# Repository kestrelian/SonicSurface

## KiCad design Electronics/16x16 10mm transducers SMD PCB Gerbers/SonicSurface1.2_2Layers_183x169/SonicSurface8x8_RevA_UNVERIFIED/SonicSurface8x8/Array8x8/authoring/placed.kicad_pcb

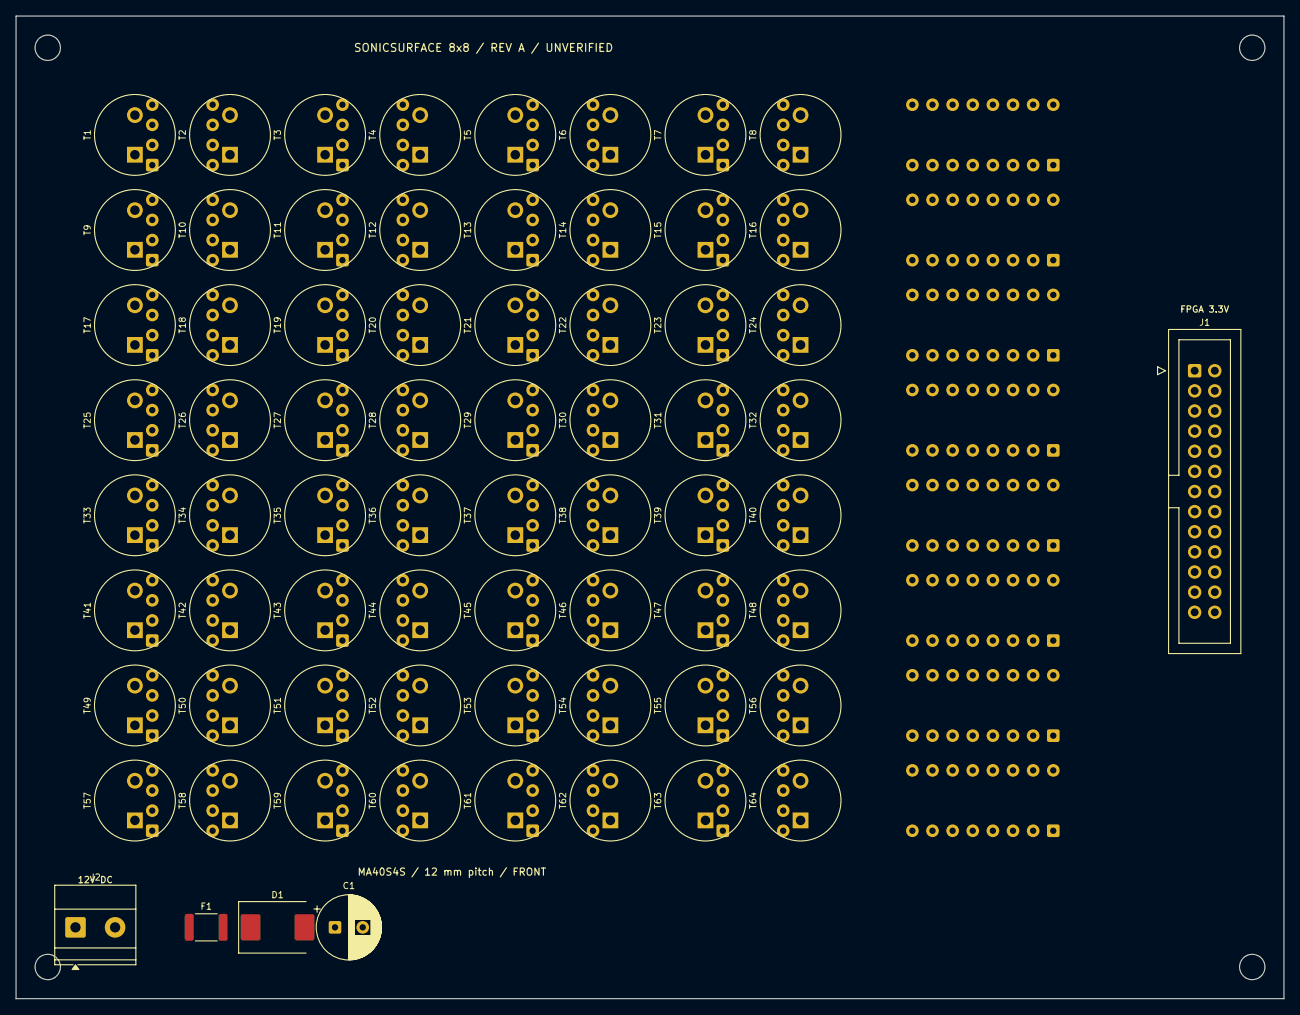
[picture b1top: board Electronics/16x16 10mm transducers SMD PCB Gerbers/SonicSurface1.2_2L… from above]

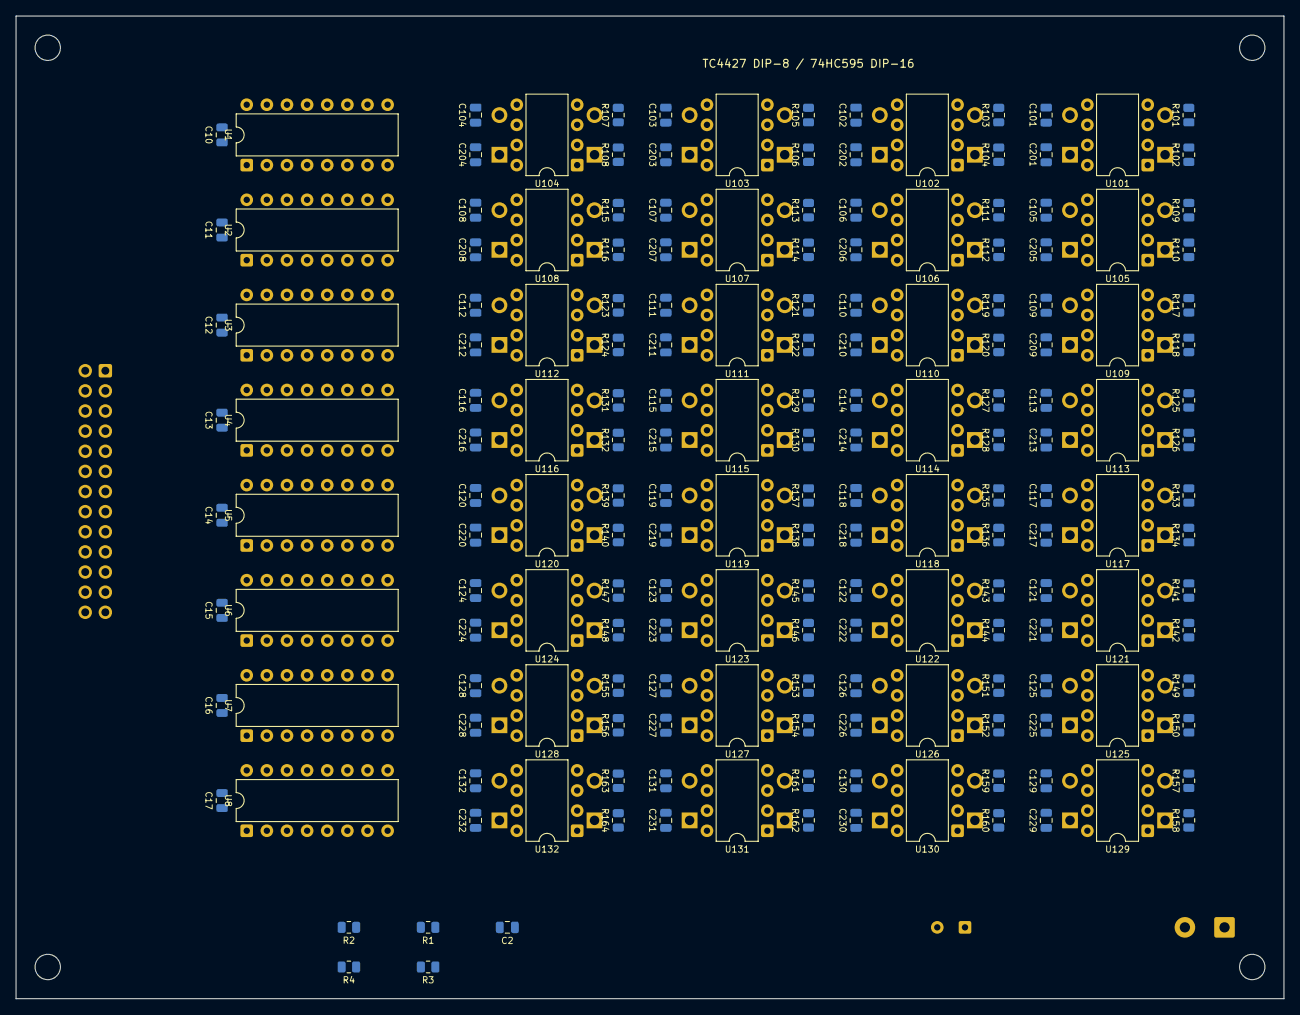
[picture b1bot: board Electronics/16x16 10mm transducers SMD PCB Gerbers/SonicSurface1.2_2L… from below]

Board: 2 copper layers, 160.0 x 124.0 mm, 254 parts (181 on the bottom side), 145 nets, no tracks yet.

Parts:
C1: 220uF 35V low ESR; CP_Radial_D8.0mm_P3.50mm
C2: 10uF 10V X7R; C_0805_2012Metric
C10, C11, C12, C13, C14, C15, C16, C17, C101, C102, C103, C104, C105, C106, C107, C108, C109, C110, C111, C112, C113, C114, C115, C116, C117, C118, C119, C120, C121, C122, C123, C124, C125, C126, C127, C128, C129, C130, C131, C132: 100nF 50V X7R; C_0805_2012Metric
C201, C202, C203, C204, C205, C206, C207, C208, C209, C210, C211, C212, C213, C214, C215, C216, C217, C218, C219, C220, C221, C222, C223, C224, C225, C226, C227, C228, C229, C230, C231, C232: 1uF 50V X7R; C_0805_2012Metric
D1: SS34 / SMC; D_SMC
F1: 1A fast / 1812; Fuse_1812_4532Metric
H1, H2, H3, H4: MountingHole_3.2mm_M3
J1: IDC26 / FPGA CABLE; IDC-Header_2x13_P2.54mm_Vertical
J2: 12V DC INPUT; TerminalBlock_Phoenix_MKDS-1,5-2_1x02_P5.00mm_Horizontal
R1, R2, R3, R4, R101, R102, R103, R104, R105, R106, R107, R108, R109, R110, R111, R112, R113, R114, R115, R116, R117, R118, R119, R120, R121, R122, R123, R124, R125, R126, R127, R128, R129, R130, R131, R132, R133, R134, R135, R136, R137, R138, R139, R140, R141, R142, R143, R144, R145, R146, R147, R148, R149, R150, R151, R152, R153, R154, R155, R156, R157, R158, R159, R160, R161, R162, R163, R164: 10k; R_0805_2012Metric
T1, T2, T3, T4, T5, T6, T7, T8, T9, T10, T11, T12, T13, T14, T15, T16, T17, T18, T19, T20, T21, T22, T23, T24, T25, T26, T27, T28, T29, T30, T31, T32, T33, T34, T35, T36, T37, T38, T39, T40, T41, T42, T43, T44, T45, T46, T47, T48, T49, T50, T51, T52, T53, T54, T55, T56, T57, T58, T59, T60, T61, T62, T63, T64: MA40S4S; MA40S4S_P5mm
U1, U2, U3, U4, U5, U6, U7, U8: 74HC595N / DIP-16; DIP-16_W7.62mm
U101, U102, U103, U104, U105, U106, U107, U108, U109, U110, U111, U112, U113, U114, U115, U116, U117, U118, U119, U120, U121, U122, U123, U124, U125, U126, U127, U128, U129, U130, U131, U132: TC4427EPA / DIP-8; DIP-8_W7.62mm

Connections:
+3V3: C2.1, C10.1, C11.1, C12.1, C13.1, C14.1, C15.1, C16.1, C17.1, J1.1, R1.1, U1.16, U2.16, U3.16, U4.16, U5.16, U6.16, U7.16, U8.16
+12V: C1.1, C101.1, C102.1, C103.1, C104.1, C105.1, C106.1, C107.1, C108.1, C109.1, C110.1, C111.1, C112.1, C113.1, C114.1, C115.1, C116.1, C117.1, C118.1, C119.1, C120.1, C121.1, C122.1, C123.1, C124.1, C125.1, C126.1, C127.1, C128.1, C129.1, C130.1, C131.1, C132.1, C201.1, C202.1, C203.1, C204.1, C205.1, C206.1, C207.1, C208.1, C209.1, C210.1, C211.1, C212.1, C213.1, C214.1, C215.1, C216.1, C217.1, C218.1, C219.1, C220.1, C221.1, C222.1, C223.1, C224.1, C225.1, C226.1, C227.1, C228.1, C229.1, C230.1, C231.1, C232.1, D1.1, U101.6, U102.6, U103.6, U104.6, U105.6, U106.6, U107.6, U108.6, U109.6, U110.6, U111.6, U112.6, U113.6, U114.6, U115.6, U116.6, U117.6, U118.6, U119.6, U120.6, U121.6, U122.6, U123.6, U124.6, U125.6, U126.6, U127.6, U128.6, U129.6, U130.6, U131.6, U132.6
CLR_N: J1.25, R2.1, U1.10, U2.10, U3.10, U4.10, U5.10, U6.10, U7.10, U8.10
DATA0: J1.3, U1.14
DATA1: J1.5, U2.14
DATA2: J1.7, U3.14
DATA3: J1.9, U4.14
DATA4: J1.11, U5.14
DATA5: J1.13, U6.14
DATA6: J1.15, U7.14
DATA7: J1.17, U8.14
DRV00: T1.1, U101.7
DRV01: T2.1, U101.5
DRV02: T3.1, U102.7
DRV03: T4.1, U102.5
DRV04: T5.1, U103.7
DRV05: T6.1, U103.5
DRV06: T7.1, U104.7
DRV07: T8.1, U104.5
DRV08: T9.1, U105.7
DRV09: T10.1, U105.5
DRV10: T11.1, U106.7
DRV11: T12.1, U106.5
DRV12: T13.1, U107.7
DRV13: T14.1, U107.5
DRV14: T15.1, U108.7
DRV15: T16.1, U108.5
DRV16: T17.1, U109.7
DRV17: T18.1, U109.5
DRV18: T19.1, U110.7
DRV19: T20.1, U110.5
DRV20: T21.1, U111.7
DRV21: T22.1, U111.5
DRV22: T23.1, U112.7
DRV23: T24.1, U112.5
DRV24: T25.1, U113.7
DRV25: T26.1, U113.5
DRV26: T27.1, U114.7
DRV27: T28.1, U114.5
DRV28: T29.1, U115.7
DRV29: T30.1, U115.5
DRV30: T31.1, U116.7
DRV31: T32.1, U116.5
DRV32: T33.1, U117.7
DRV33: T34.1, U117.5
DRV34: T35.1, U118.7
DRV35: T36.1, U118.5
DRV36: T37.1, U119.7
DRV37: T38.1, U119.5
DRV38: T39.1, U120.7
DRV39: T40.1, U120.5
DRV40: T41.1, U121.7
DRV41: T42.1, U121.5
DRV42: T43.1, U122.7
DRV43: T44.1, U122.5
DRV44: T45.1, U123.7
DRV45: T46.1, U123.5
DRV46: T47.1, U124.7
DRV47: T48.1, U124.5
DRV48: T49.1, U125.7
DRV49: T50.1, U125.5
DRV50: T51.1, U126.7
DRV51: T52.1, U126.5
DRV52: T53.1, U127.7
DRV53: T54.1, U127.5
DRV54: T55.1, U128.7
DRV55: T56.1, U128.5
DRV56: T57.1, U129.7
DRV57: T58.1, U129.5
DRV58: T59.1, U130.7
DRV59: T60.1, U130.5
DRV60: T61.1, U131.7
DRV61: T62.1, U131.5
DRV62: T63.1, U132.7
DRV63: T64.1, U132.5
GND: C1.2, C2.2, C10.2, C11.2, C12.2, C13.2, C14.2, C15.2, C16.2, C17.2, C101.2, C102.2, C103.2, C104.2, C105.2, C106.2, C107.2, C108.2, C109.2, C110.2, C111.2, C112.2, C113.2, C114.2, C115.2, C116.2, C117.2, C118.2, C119.2, C120.2, C121.2, C122.2, C123.2, C124.2, C125.2, C126.2, C127.2, C128.2, C129.2, C130.2, C131.2, C132.2, C201.2, C202.2, C203.2, C204.2, C205.2, C206.2, C207.2, C208.2, C209.2, C210.2, C211.2, C212.2, C213.2, C214.2, C215.2, C216.2, C217.2, C218.2, C219.2, C220.2, C221.2, C222.2, C223.2, C224.2, C225.2, C226.2, C227.2, C228.2, C229.2, C230.2, C231.2, C232.2, J1.2, J1.4, J1.6, J1.8, J1.10, J1.12, J1.14, J1.16, J1.18, J1.20, J1.22, J1.24, J1.26, J2.2, R2.2, R3.2, R4.2, R101.2, R102.2, R103.2, R104.2, R105.2, R106.2, R107.2, R108.2, R109.2, R110.2, R111.2, R112.2, R113.2, R114.2, R115.2, R116.2, R117.2, R118.2, R119.2, R120.2, R121.2, R122.2, R123.2, R124.2, R125.2, R126.2, R127.2, R128.2, R129.2, R130.2, R131.2, R132.2, R133.2, R134.2, R135.2, R136.2, R137.2, R138.2, R139.2, R140.2, R141.2, R142.2, R143.2, R144.2, R145.2, R146.2, R147.2, R148.2, R149.2, R150.2, R151.2, R152.2, R153.2, R154.2, R155.2, R156.2, R157.2, R158.2, R159.2, R160.2, R161.2, R162.2, R163.2, R164.2, T1.2, T2.2, T3.2, T4.2, T5.2, T6.2, T7.2, T8.2, T9.2, T10.2, T11.2, T12.2, T13.2, T14.2, T15.2, T16.2, T17.2, T18.2, T19.2, T20.2, T21.2, T22.2, T23.2, T24.2, T25.2, T26.2, T27.2, T28.2, T29.2, T30.2, T31.2, T32.2, T33.2, T34.2, T35.2, T36.2, T37.2, T38.2, T39.2, T40.2, T41.2, T42.2, T43.2, T44.2, T45.2, T46.2, T47.2, T48.2, T49.2, T50.2, T51.2, T52.2, T53.2, T54.2, T55.2, T56.2, T57.2, T58.2, T59.2, T60.2, T61.2, T62.2, T63.2, T64.2, U1.8, U2.8, U3.8, U4.8, U5.8, U6.8, U7.8, U8.8, U101.3, U102.3, U103.3, U104.3, U105.3, U106.3, U107.3, U108.3, U109.3, U110.3, U111.3, U112.3, U113.3, U114.3, U115.3, U116.3, U117.3, U118.3, U119.3, U120.3, U121.3, U122.3, U123.3, U124.3, U125.3, U126.3, U127.3, U128.3, U129.3, U130.3, U131.3, U132.3
LATCH: J1.21, R4.1, U1.12, U2.12, U3.12, U4.12, U5.12, U6.12, U7.12, U8.12
OE_N: J1.23, R1.2, U1.13, U2.13, U3.13, U4.13, U5.13, U6.13, U7.13, U8.13
Q00: R101.1, U1.15, U101.2
Q01: R102.1, U1.1, U101.4
Q02: R103.1, U1.2, U102.2
Q03: R104.1, U1.3, U102.4
Q04: R105.1, U1.4, U103.2
Q05: R106.1, U1.5, U103.4
Q06: R107.1, U1.6, U104.2
Q07: R108.1, U1.7, U104.4
Q08: R109.1, U2.15, U105.2
Q09: R110.1, U2.1, U105.4
Q10: R111.1, U2.2, U106.2
Q11: R112.1, U2.3, U106.4
Q12: R113.1, U2.4, U107.2
Q13: R114.1, U2.5, U107.4
Q14: R115.1, U2.6, U108.2
Q15: R116.1, U2.7, U108.4
Q16: R117.1, U3.15, U109.2
Q17: R118.1, U3.1, U109.4
Q18: R119.1, U3.2, U110.2
Q19: R120.1, U3.3, U110.4
Q20: R121.1, U3.4, U111.2
Q21: R122.1, U3.5, U111.4
Q22: R123.1, U3.6, U112.2
Q23: R124.1, U3.7, U112.4
Q24: R125.1, U4.15, U113.2
Q25: R126.1, U4.1, U113.4
Q26: R127.1, U4.2, U114.2
Q27: R128.1, U4.3, U114.4
Q28: R129.1, U4.4, U115.2
Q29: R130.1, U4.5, U115.4
Q30: R131.1, U4.6, U116.2
Q31: R132.1, U4.7, U116.4
Q32: R133.1, U5.15, U117.2
Q33: R134.1, U5.1, U117.4
Q34: R135.1, U5.2, U118.2
Q35: R136.1, U5.3, U118.4
Q36: R137.1, U5.4, U119.2
Q37: R138.1, U5.5, U119.4
Q38: R139.1, U5.6, U120.2
Q39: R140.1, U5.7, U120.4
Q40: R141.1, U6.15, U121.2
Q41: R142.1, U6.1, U121.4
Q42: R143.1, U6.2, U122.2
Q43: R144.1, U6.3, U122.4
Q44: R145.1, U6.4, U123.2
Q45: R146.1, U6.5, U123.4
Q46: R147.1, U6.6, U124.2
Q47: R148.1, U6.7, U124.4
Q48: R149.1, U7.15, U125.2
Q49: R150.1, U7.1, U125.4
Q50: R151.1, U7.2, U126.2
Q51: R152.1, U7.3, U126.4
Q52: R153.1, U7.4, U127.2
Q53: R154.1, U7.5, U127.4
Q54: R155.1, U7.6, U128.2
Q55: R156.1, U7.7, U128.4
Q56: R157.1, U8.15, U129.2
Q57: R158.1, U8.1, U129.4
Q58: R159.1, U8.2, U130.2
Q59: R160.1, U8.3, U130.4
Q60: R161.1, U8.4, U131.2
Q61: R162.1, U8.5, U131.4
Q62: R163.1, U8.6, U132.2
Q63: R164.1, U8.7, U132.4
SCLK: J1.19, R3.1, U1.11, U2.11, U3.11, U4.11, U5.11, U6.11, U7.11, U8.11
VFUSED: D1.2, F1.2
VIN: F1.1, J2.1

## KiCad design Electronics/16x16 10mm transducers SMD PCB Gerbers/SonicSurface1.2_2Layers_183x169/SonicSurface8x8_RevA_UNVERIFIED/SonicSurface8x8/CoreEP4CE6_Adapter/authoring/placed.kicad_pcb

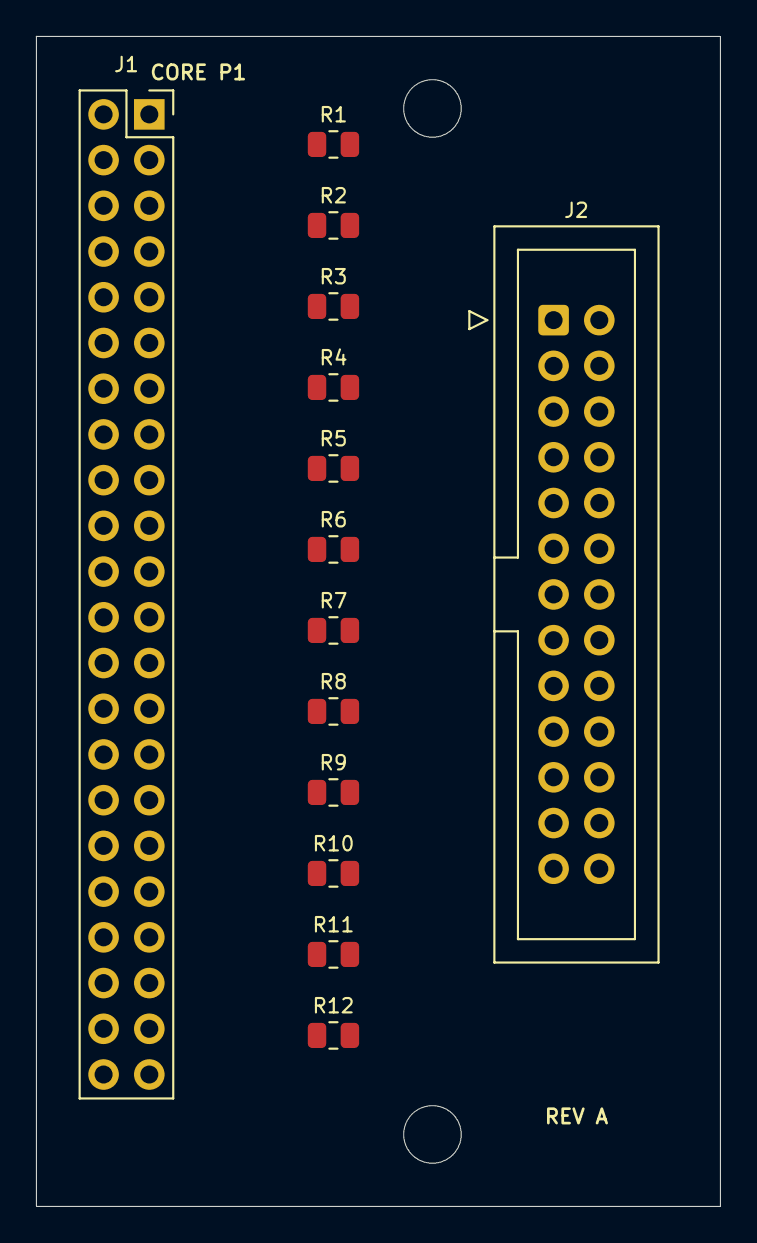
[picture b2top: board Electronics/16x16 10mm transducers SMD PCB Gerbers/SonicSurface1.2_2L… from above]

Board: 2 copper layers, 38.0 x 65.0 mm, 16 parts (0 on the bottom side), 26 nets, no tracks yet.

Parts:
H1, H2: MountingHole_3.2mm_M3
J1: CoreEP4CE6 P1 ONLY; PinSocket_2x22_P2.54mm_Vertical
J2: IDC26 to ARRAY J1; IDC-Header_2x13_P2.54mm_Vertical
R1, R2, R3, R4, R5, R6, R7, R8, R9, R10, R11, R12: 33R source termination; R_0805_2012Metric

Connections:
+3V3: J1.2, J2.1
CLR_N: J2.25, R12.2
CLR_N_SRC: J1.20, R12.1
DATA0: J2.3, R1.2
DATA0_SRC: J1.3, R1.1
DATA1: J2.5, R2.2
DATA1_SRC: J1.5, R2.1
DATA2: J2.7, R3.2
DATA2_SRC: J1.7, R3.1
DATA3: J2.9, R4.2
DATA3_SRC: J1.9, R4.1
DATA4: J2.11, R5.2
DATA4_SRC: J1.11, R5.1
DATA5: J2.13, R6.2
DATA5_SRC: J1.13, R6.1
DATA6: J2.15, R7.2
DATA6_SRC: J1.15, R7.1
DATA7: J2.17, R8.2
DATA7_SRC: J1.17, R8.1
GND: J1.1, J1.23, J2.2, J2.4, J2.6, J2.8, J2.10, J2.12, J2.14, J2.16, J2.18, J2.20, J2.22, J2.24, J2.26
LATCH: J2.21, R10.2
LATCH_SRC: J1.22, R10.1
OE_N: J2.23, R11.2
OE_N_SRC: J1.19, R11.1
SCLK: J2.19, R9.2
SCLK_SRC: J1.21, R9.1

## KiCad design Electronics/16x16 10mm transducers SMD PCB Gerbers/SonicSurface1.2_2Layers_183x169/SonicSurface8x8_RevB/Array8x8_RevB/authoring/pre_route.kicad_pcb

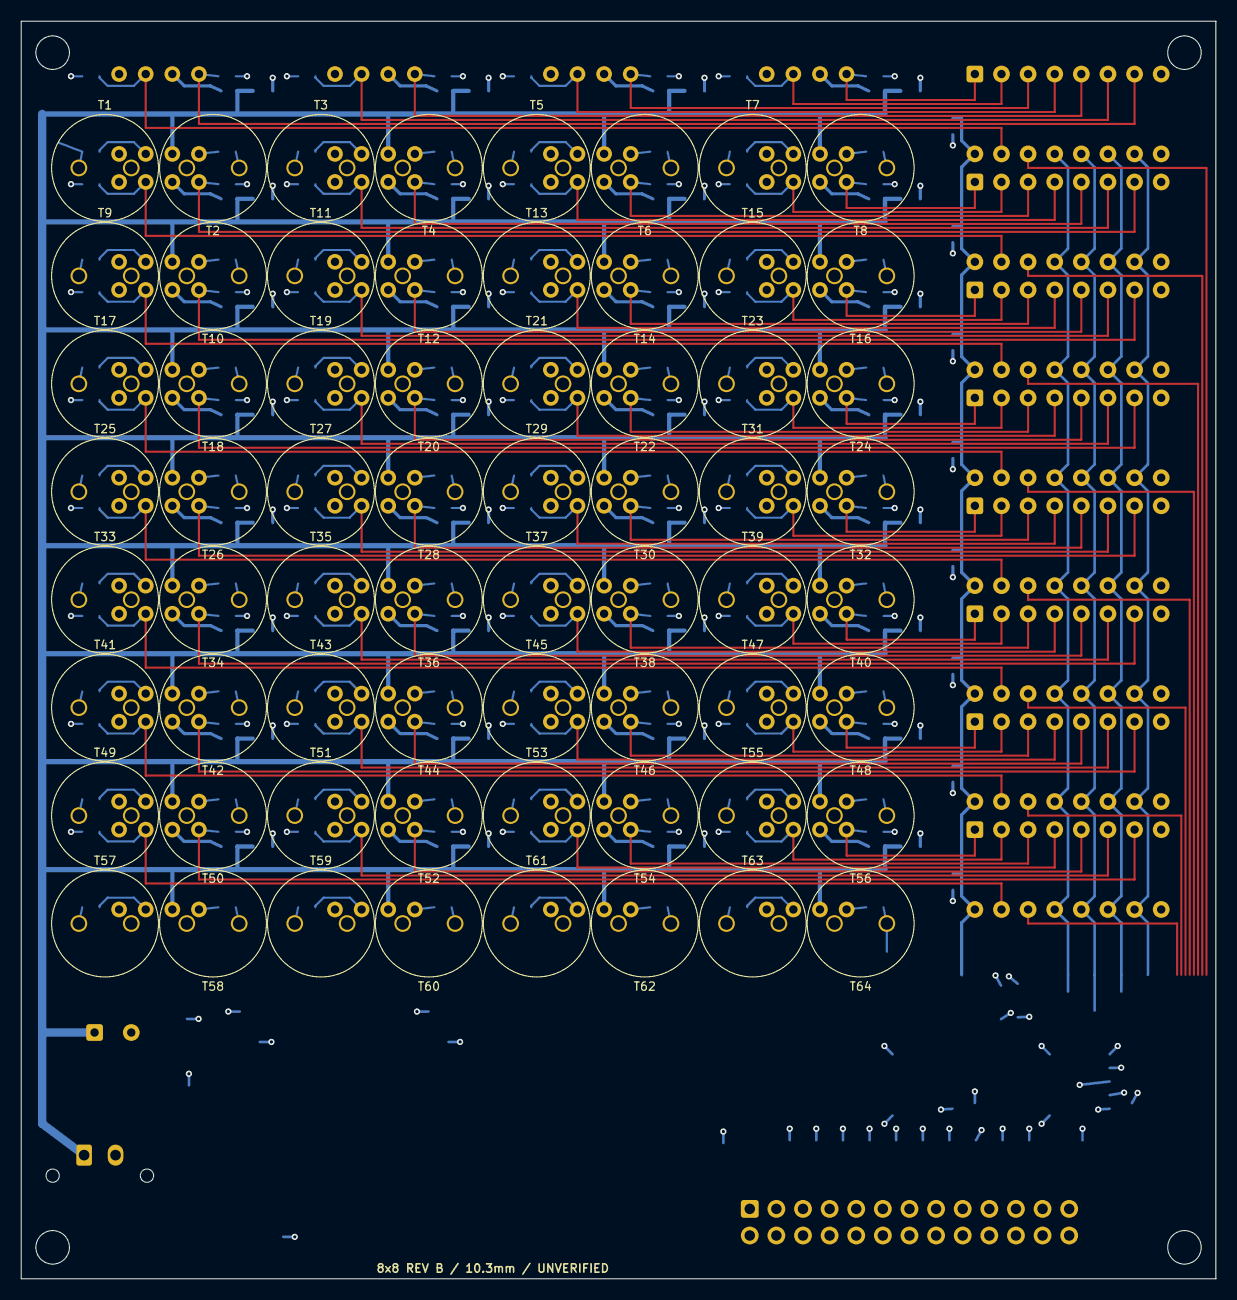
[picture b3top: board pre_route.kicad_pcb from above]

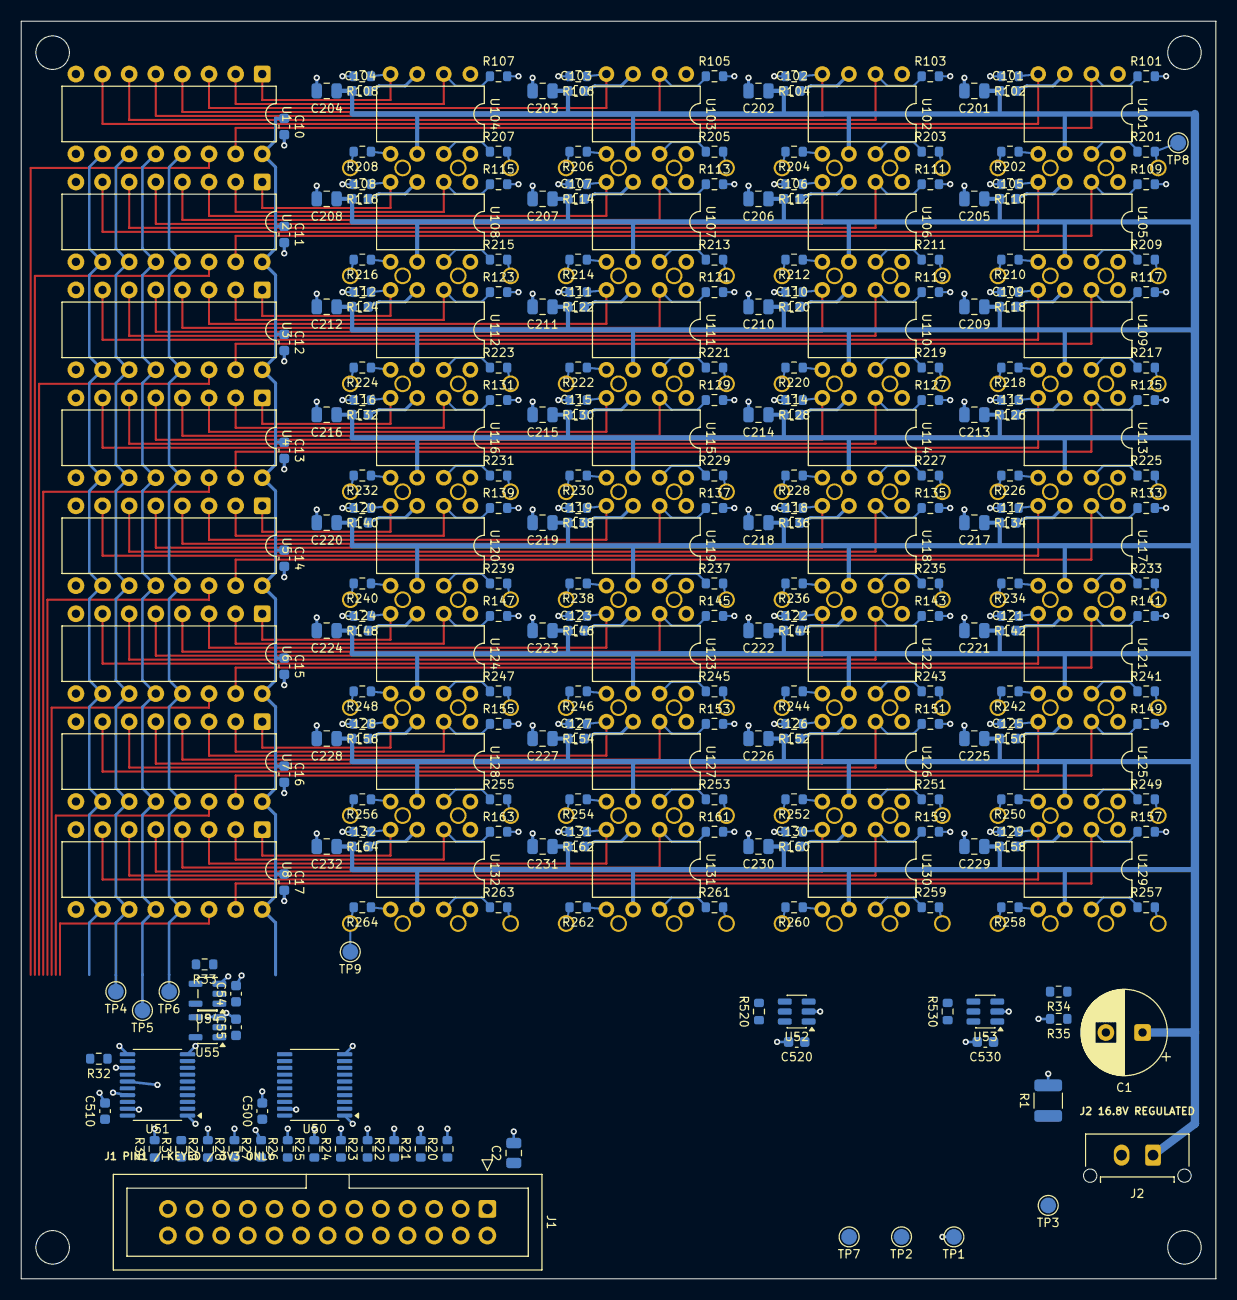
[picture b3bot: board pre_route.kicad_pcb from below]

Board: 2 copper layers, 114.0 x 120.0 mm, 352 parts (284 on the bottom side), 224 nets.

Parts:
C1: 220uF 35V low ESR; CP_Radial_D8.0mm_P3.50mm
C2: 10uF 10V X7R; C_0805_2012Metric
C10, C11, C12, C13, C14, C15, C16, C17, C54, C55, C101, C102, C103, C104, C105, C106, C107, C108, C109, C110, C111, C112, C113, C114, C115, C116, C117, C118, C119, C120, C121, C122, C123, C124, C125, C126, C127, C128, C129, C130, C131, C132, C500, C510, C520, C530: 100nF 50V X7R; C_0603_1608Metric
C201, C202, C203, C204, C205, C206, C207, C208, C209, C210, C211, C212, C213, C214, C215, C216, C217, C218, C219, C220, C221, C222, C223, C224, C225, C226, C227, C228, C229, C230, C231, C232: 1uF 50V X7R; C_0805_2012Metric
H1, H2, H3, H4: MountingHole_3.2mm_M3
J1: KEYED IDC26 / 100mm MAX; IDC-Header_2x13_P2.54mm_Vertical
J2: REGULATED DRIVER POWER ONLY; FP_910b6471cdf1
R1: 2.2k 0.5W discharge; R_1210_3225Metric
R20, R21, R22, R23, R24, R25, R26, R27, R28, R29, R30: 100k; R_0603_1608Metric
R31, R32, R33, R101, R102, R103, R104, R105, R106, R107, R108, R109, R110, R111, R112, R113, R114, R115, R116, R117, R118, R119, R120, R121, R122, R123, R124, R125, R126, R127, R128, R129, R130, R131, R132, R133, R134, R135, R136, R137, R138, R139, R140, R141, R142, R143, R144, R145, R146, R147, R148, R149, R150, R151, R152, R153, R154, R155, R156, R157, R158, R159, R160, R161, R162, R163, R164, R520, R530: 10k; R_0603_1608Metric
R34: 374k 0.1%; R_0603_1608Metric
R35: 10k 0.1%; R_0603_1608Metric
R201, R202, R203, R204, R205, R206, R207, R208, R209, R210, R211, R212, R213, R214, R215, R216, R217, R218, R219, R220, R221, R222, R223, R224, R225, R226, R227, R228, R229, R230, R231, R232, R233, R234, R235, R236, R237, R238, R239, R240, R241, R242, R243, R244, R245, R246, R247, R248, R249, R250, R251, R252, R253, R254, R255, R256, R257, R258, R259, R260, R261, R262, R263, R264: 22R damping; R_0603_1608Metric
T1, T2, T3, T4, T5, T6, T7, T8, T9, T10, T11, T12, T13, T14, T15, T16, T17, T18, T19, T20, T21, T22, T23, T24, T25, T26, T27, T28, T29, T30, T31, T32, T33, T34, T35, T36, T37, T38, T39, T40, T41, T42, T43, T44, T45, T46, T47, T48, T49, T50, T51, T52, T53, T54, T55, T56, T57, T58, T59, T60, T61, T62, T63, T64: MA40S4S; MA40S4S_P5mm
TP1: GND; TestPoint_Pad_D1.5mm
TP2: +3V3; TestPoint_Pad_D1.5mm
TP3: VDRV; TestPoint_Pad_D1.5mm
TP4: SCLK; TestPoint_Pad_D1.5mm
TP5: LATCH; TestPoint_Pad_D1.5mm
TP6: OE_LOCAL_N; TestPoint_Pad_D1.5mm
TP7: RAILS_OK; TestPoint_Pad_D1.5mm
TP8: DRV00; TestPoint_Pad_D1.5mm
TP9: DRV63; TestPoint_Pad_D1.5mm
U1, U2, U3, U4, U5, U6, U7, U8: SN74HC595N DIP-16; DIP-16_W7.62mm
U50, U51: SN74LVC244APW / Ioff; TSSOP-20_4.4x6.5mm_P0.65mm
U52: TPS3808G33DBVR; SOT-23-6
U53: TPS3808G01DBVR; SOT-23-6
U54: SN74LVC1G04DBVR; SOT-23-5
U55: SN74LVC1G32DBVR; SOT-23-5
U101, U102, U103, U104, U105, U106, U107, U108, U109, U110, U111, U112, U113, U114, U115, U116, U117, U118, U119, U120, U121, U122, U123, U124, U125, U126, U127, U128, U129, U130, U131, U132: TC4427EPA DIP-8; DIP-8_W7.62mm

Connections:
+3V3: C2.1, C10.1, C11.1, C12.1, C13.1, C14.1, C15.1, C16.1, C17.1, C54.1, C55.1, C500.1, C510.1, C520.1, C530.1, J1.1, R31.2, R32.2, R33.2, R520.2, R530.2, TP2.1, U1.16, U2.16, U3.16, U4.16, U5.16, U6.16, U7.16, U8.16, U50.20, U51.20, U52.3, U52.5, U52.6, U53.6, U54.5, U55.5
CLR_N: U1.10, U2.10, U3.10, U4.10, U5.10, U6.10, U7.10, U8.10, U51.12
CLR_N_RX: J1.25, R30.1, U51.8
DATA0: U1.14, U50.18
DATA0_RX: J1.3, R20.1, U50.2
DATA1: U2.14, U50.16
DATA1_RX: J1.5, R21.1, U50.4
DATA2: U3.14, U50.14
DATA2_RX: J1.7, R22.1, U50.6
DATA3: U4.14, U50.12
DATA3_RX: J1.9, R23.1, U50.8
DATA4: U5.14, U50.9
DATA4_RX: J1.11, R24.1, U50.11
DATA5: U6.14, U50.7
DATA5_RX: J1.13, R25.1, U50.13
DATA6: U7.14, U50.5
DATA6_RX: J1.15, R26.1, U50.15
DATA7: U8.14, U50.3
DATA7_RX: J1.17, R27.1, U50.17
DRV00: R201.2, T1.1, TP8.1
DRV01: R202.2, T2.1
DRV02: R203.2, T3.1
DRV03: R204.2, T4.1
DRV04: R205.2, T5.1
DRV05: R206.2, T6.1
DRV06: R207.2, T7.1
DRV07: R208.2, T8.1
DRV08: R209.2, T9.1
DRV09: R210.2, T10.1
DRV10: R211.2, T11.1
DRV11: R212.2, T12.1
DRV12: R213.2, T13.1
DRV13: R214.2, T14.1
DRV14: R215.2, T15.1
DRV15: R216.2, T16.1
DRV16: R217.2, T17.1
DRV17: R218.2, T18.1
DRV18: R219.2, T19.1
DRV19: R220.2, T20.1
DRV20: R221.2, T21.1
DRV21: R222.2, T22.1
DRV22: R223.2, T23.1
DRV23: R224.2, T24.1
DRV24: R225.2, T25.1
DRV25: R226.2, T26.1
DRV26: R227.2, T27.1
DRV27: R228.2, T28.1
DRV28: R229.2, T29.1
DRV29: R230.2, T30.1
DRV30: R231.2, T31.1
DRV31: R232.2, T32.1
DRV32: R233.2, T33.1
DRV33: R234.2, T34.1
DRV34: R235.2, T35.1
DRV35: R236.2, T36.1
DRV36: R237.2, T37.1
DRV37: R238.2, T38.1
DRV38: R239.2, T39.1
DRV39: R240.2, T40.1
DRV40: R241.2, T41.1
DRV41: R242.2, T42.1
DRV42: R243.2, T43.1
DRV43: R244.2, T44.1
DRV44: R245.2, T45.1
DRV45: R246.2, T46.1
DRV46: R247.2, T47.1
DRV47: R248.2, T48.1
DRV48: R249.2, T49.1
DRV49: R250.2, T50.1
DRV50: R251.2, T51.1
DRV51: R252.2, T52.1
DRV52: R253.2, T53.1
DRV53: R254.2, T54.1
DRV54: R255.2, T55.1
DRV55: R256.2, T56.1
DRV56: R257.2, T57.1
DRV57: R258.2, T58.1
DRV58: R259.2, T59.1
DRV59: R260.2, T60.1
DRV60: R261.2, T61.1
DRV61: R262.2, T62.1
DRV62: R263.2, T63.1
DRV63: R264.2, T64.1, TP9.1
DRV_SENSE: R34.2, R35.1, U53.5
GND: C1.2, C2.2, C10.2, C11.2, C12.2, C13.2, C14.2, C15.2, C16.2, C17.2, C54.2, C55.2, C101.2, C102.2, C103.2, C104.2, C105.2, C106.2, C107.2, C108.2, C109.2, C110.2, C111.2, C112.2, C113.2, C114.2, C115.2, C116.2, C117.2, C118.2, C119.2, C120.2, C121.2, C122.2, C123.2, C124.2, C125.2, C126.2, C127.2, C128.2, C129.2, C130.2, C131.2, C132.2, C201.2, C202.2, C203.2, C204.2, C205.2, C206.2, C207.2, C208.2, C209.2, C210.2, C211.2, C212.2, C213.2, C214.2, C215.2, C216.2, C217.2, C218.2, C219.2, C220.2, C221.2, C222.2, C223.2, C224.2, C225.2, C226.2, C227.2, C228.2, C229.2, C230.2, C231.2, C232.2, C500.2, C510.2, C520.2, C530.2, J1.2, J1.4, J1.6, J1.8, J1.10, J1.12, J1.14, J1.16, J1.18, J1.20, J1.22, J1.24, J1.26, J2.2, R1.2, R20.2, R21.2, R22.2, R23.2, R24.2, R25.2, R26.2, R27.2, R28.2, R29.2, R30.2, R35.2, R101.2, R102.2, R103.2, R104.2, R105.2, R106.2, R107.2, R108.2, R109.2, R110.2, R111.2, R112.2, R113.2, R114.2, R115.2, R116.2, R117.2, R118.2, R119.2, R120.2, R121.2, R122.2, R123.2, R124.2, R125.2, R126.2, R127.2, R128.2, R129.2, R130.2, R131.2, R132.2, R133.2, R134.2, R135.2, R136.2, R137.2, R138.2, R139.2, R140.2, R141.2, R142.2, R143.2, R144.2, R145.2, R146.2, R147.2, R148.2, R149.2, R150.2, R151.2, R152.2, R153.2, R154.2, R155.2, R156.2, R157.2, R158.2, R159.2, R160.2, R161.2, R162.2, R163.2, R164.2, T1.2, T2.2, T3.2, T4.2, T5.2, T6.2, T7.2, T8.2, T9.2, T10.2, T11.2, T12.2, T13.2, T14.2, T15.2, T16.2, T17.2, T18.2, T19.2, T20.2, T21.2, T22.2, T23.2, T24.2, T25.2, T26.2, T27.2, T28.2, T29.2, T30.2, T31.2, T32.2, T33.2, T34.2, T35.2, T36.2, T37.2, T38.2, T39.2, T40.2, T41.2, T42.2, T43.2, T44.2, T45.2, T46.2, T47.2, T48.2, T49.2, T50.2, T51.2, T52.2, T53.2, T54.2, T55.2, T56.2, T57.2, T58.2, T59.2, T60.2, T61.2, T62.2, T63.2, T64.2, TP1.1, U1.8, U2.8, U3.8, U4.8, U5.8, U6.8, U7.8, U8.8, U50.1, U50.10, U50.19, U51.1, U51.10, U51.11, U51.13, U51.15, U51.17, U51.19, U52.2, U53.2, U54.3, U55.3, U101.3, U102.3, U103.3, U104.3, U105.3, U106.3, U107.3, U108.3, U109.3, U110.3, U111.3, U112.3, U113.3, U114.3, U115.3, U116.3, U117.3, U118.3, U119.3, U120.3, U121.3, U122.3, U123.3, U124.3, U125.3, U126.3, U127.3, U128.3, U129.3, U130.3, U131.3, U132.3
LATCH: TP5.1, U1.12, U2.12, U3.12, U4.12, U5.12, U6.12, U7.12, U8.12, U51.16
LATCH_RX: J1.21, R29.1, U51.4
LOGIC_OK: R520.1, U52.1, U53.3
OE_CMD_N: R32.1, U51.14, U55.2
OE_LOCAL_N: R33.1, TP6.1, U1.13, U2.13, U3.13, U4.13, U5.13, U6.13, U7.13, U8.13, U55.4
OE_N_RX: J1.23, R31.1, U51.6
OUT00: R201.1, U101.7
OUT01: R202.1, U101.5
OUT02: R203.1, U102.7
OUT03: R204.1, U102.5
OUT04: R205.1, U103.7
OUT05: R206.1, U103.5
OUT06: R207.1, U104.7
OUT07: R208.1, U104.5
OUT08: R209.1, U105.7
OUT09: R210.1, U105.5
OUT10: R211.1, U106.7
OUT11: R212.1, U106.5
OUT12: R213.1, U107.7
OUT13: R214.1, U107.5
OUT14: R215.1, U108.7
OUT15: R216.1, U108.5
OUT16: R217.1, U109.7
OUT17: R218.1, U109.5
OUT18: R219.1, U110.7
OUT19: R220.1, U110.5
OUT20: R221.1, U111.7
OUT21: R222.1, U111.5
OUT22: R223.1, U112.7
OUT23: R224.1, U112.5
OUT24: R225.1, U113.7
OUT25: R226.1, U113.5
OUT26: R227.1, U114.7
OUT27: R228.1, U114.5
OUT28: R229.1, U115.7
OUT29: R230.1, U115.5
OUT30: R231.1, U116.7
OUT31: R232.1, U116.5
OUT32: R233.1, U117.7
OUT33: R234.1, U117.5
OUT34: R235.1, U118.7
OUT35: R236.1, U118.5
OUT36: R237.1, U119.7
OUT37: R238.1, U119.5
OUT38: R239.1, U120.7
OUT39: R240.1, U120.5
OUT40: R241.1, U121.7
OUT41: R242.1, U121.5
OUT42: R243.1, U122.7
OUT43: R244.1, U122.5
OUT44: R245.1, U123.7
OUT45: R246.1, U123.5
OUT46: R247.1, U124.7
OUT47: R248.1, U124.5
OUT48: R249.1, U125.7
OUT49: R250.1, U125.5
OUT50: R251.1, U126.7
OUT51: R252.1, U126.5
OUT52: R253.1, U127.7
OUT53: R254.1, U127.5
OUT54: R255.1, U128.7
OUT55: R256.1, U128.5
OUT56: R257.1, U129.7
OUT57: R258.1, U129.5
OUT58: R259.1, U130.7
OUT59: R260.1, U130.5
OUT60: R261.1, U131.7
OUT61: R262.1, U131.5
OUT62: R263.1, U132.7
OUT63: R264.1, U132.5
Q00: R101.1, U1.15, U101.2
Q01: R102.1, U1.7, U101.4
Q02: R103.1, U1.6, U102.2
Q03: R104.1, U1.5, U102.4
Q04: R105.1, U1.4, U103.2
Q05: R106.1, U1.3, U103.4
Q06: R107.1, U1.2, U104.2
Q07: R108.1, U1.1, U104.4
Q08: R109.1, U2.15, U105.2
Q09: R110.1, U2.7, U105.4
Q10: R111.1, U2.6, U106.2
Q11: R112.1, U2.5, U106.4
Q12: R113.1, U2.4, U107.2
Q13: R114.1, U2.3, U107.4
Q14: R115.1, U2.2, U108.2
Q15: R116.1, U2.1, U108.4
Q16: R117.1, U3.15, U109.2
Q17: R118.1, U3.7, U109.4
Q18: R119.1, U3.6, U110.2
Q19: R120.1, U3.5, U110.4
Q20: R121.1, U3.4, U111.2
Q21: R122.1, U3.3, U111.4
Q22: R123.1, U3.2, U112.2
Q23: R124.1, U3.1, U112.4
Q24: R125.1, U4.15, U113.2
Q25: R126.1, U4.7, U113.4
Q26: R127.1, U4.6, U114.2
Q27: R128.1, U4.5, U114.4
Q28: R129.1, U4.4, U115.2
Q29: R130.1, U4.3, U115.4
Q30: R131.1, U4.2, U116.2
Q31: R132.1, U4.1, U116.4
Q32: R133.1, U5.15, U117.2
Q33: R134.1, U5.7, U117.4
Q34: R135.1, U5.6, U118.2
Q35: R136.1, U5.5, U118.4
Q36: R137.1, U5.4, U119.2
Q37: R138.1, U5.3, U119.4
Q38: R139.1, U5.2, U120.2
Q39: R140.1, U5.1, U120.4
Q40: R141.1, U6.15, U121.2
Q41: R142.1, U6.7, U121.4
Q42: R143.1, U6.6, U122.2
Q43: R144.1, U6.5, U122.4
Q44: R145.1, U6.4, U123.2
Q45: R146.1, U6.3, U123.4
Q46: R147.1, U6.2, U124.2
Q47: R148.1, U6.1, U124.4
Q48: R149.1, U7.15, U125.2
Q49: R150.1, U7.7, U125.4
Q50: R151.1, U7.6, U126.2
Q51: R152.1, U7.5, U126.4
Q52: R153.1, U7.4, U127.2
Q53: R154.1, U7.3, U127.4
Q54: R155.1, U7.2, U128.2
Q55: R156.1, U7.1, U128.4
Q56: R157.1, U8.15, U129.2
Q57: R158.1, U8.7, U129.4
Q58: R159.1, U8.6, U130.2
Q59: R160.1, U8.5, U130.4
Q60: R161.1, U8.4, U131.2
Q61: R162.1, U8.3, U131.4
Q62: R163.1, U8.2, U132.2
Q63: R164.1, U8.1, U132.4
RAILS_OK: R530.1, TP7.1, U53.1, U54.2
RAIL_BAD: U54.4, U55.1
SCLK: TP4.1, U1.11, U2.11, U3.11, U4.11, U5.11, U6.11, U7.11, U8.11, U51.18
SCLK_RX: J1.19, R28.1, U51.2
VDRV: C1.1, C101.1, C102.1, C103.1, C104.1, C105.1, C106.1, C107.1, C108.1, C109.1, C110.1, C111.1, C112.1, C113.1, C114.1, C115.1, C116.1, C117.1, C118.1, C119.1, C120.1, C121.1, C122.1, C123.1, C124.1, C125.1, C126.1, C127.1, C128.1, C129.1, C130.1, C131.1, C132.1, C201.1, C202.1, C203.1, C204.1, C205.1, C206.1, C207.1, C208.1, C209.1, C210.1, C211.1, C212.1, C213.1, C214.1, C215.1, C216.1, C217.1, C218.1, C219.1, C220.1, C221.1, C222.1, C223.1, C224.1, C225.1, C226.1, C227.1, C228.1, C229.1, C230.1, C231.1, C232.1, J2.1, R1.1, R34.1, TP3.1, U101.6, U102.6, U103.6, U104.6, U105.6, U106.6, U107.6, U108.6, U109.6, U110.6, U111.6, U112.6, U113.6, U114.6, U115.6, U116.6, U117.6, U118.6, U119.6, U120.6, U121.6, U122.6, U123.6, U124.6, U125.6, U126.6, U127.6, U128.6, U129.6, U130.6, U131.6, U132.6
